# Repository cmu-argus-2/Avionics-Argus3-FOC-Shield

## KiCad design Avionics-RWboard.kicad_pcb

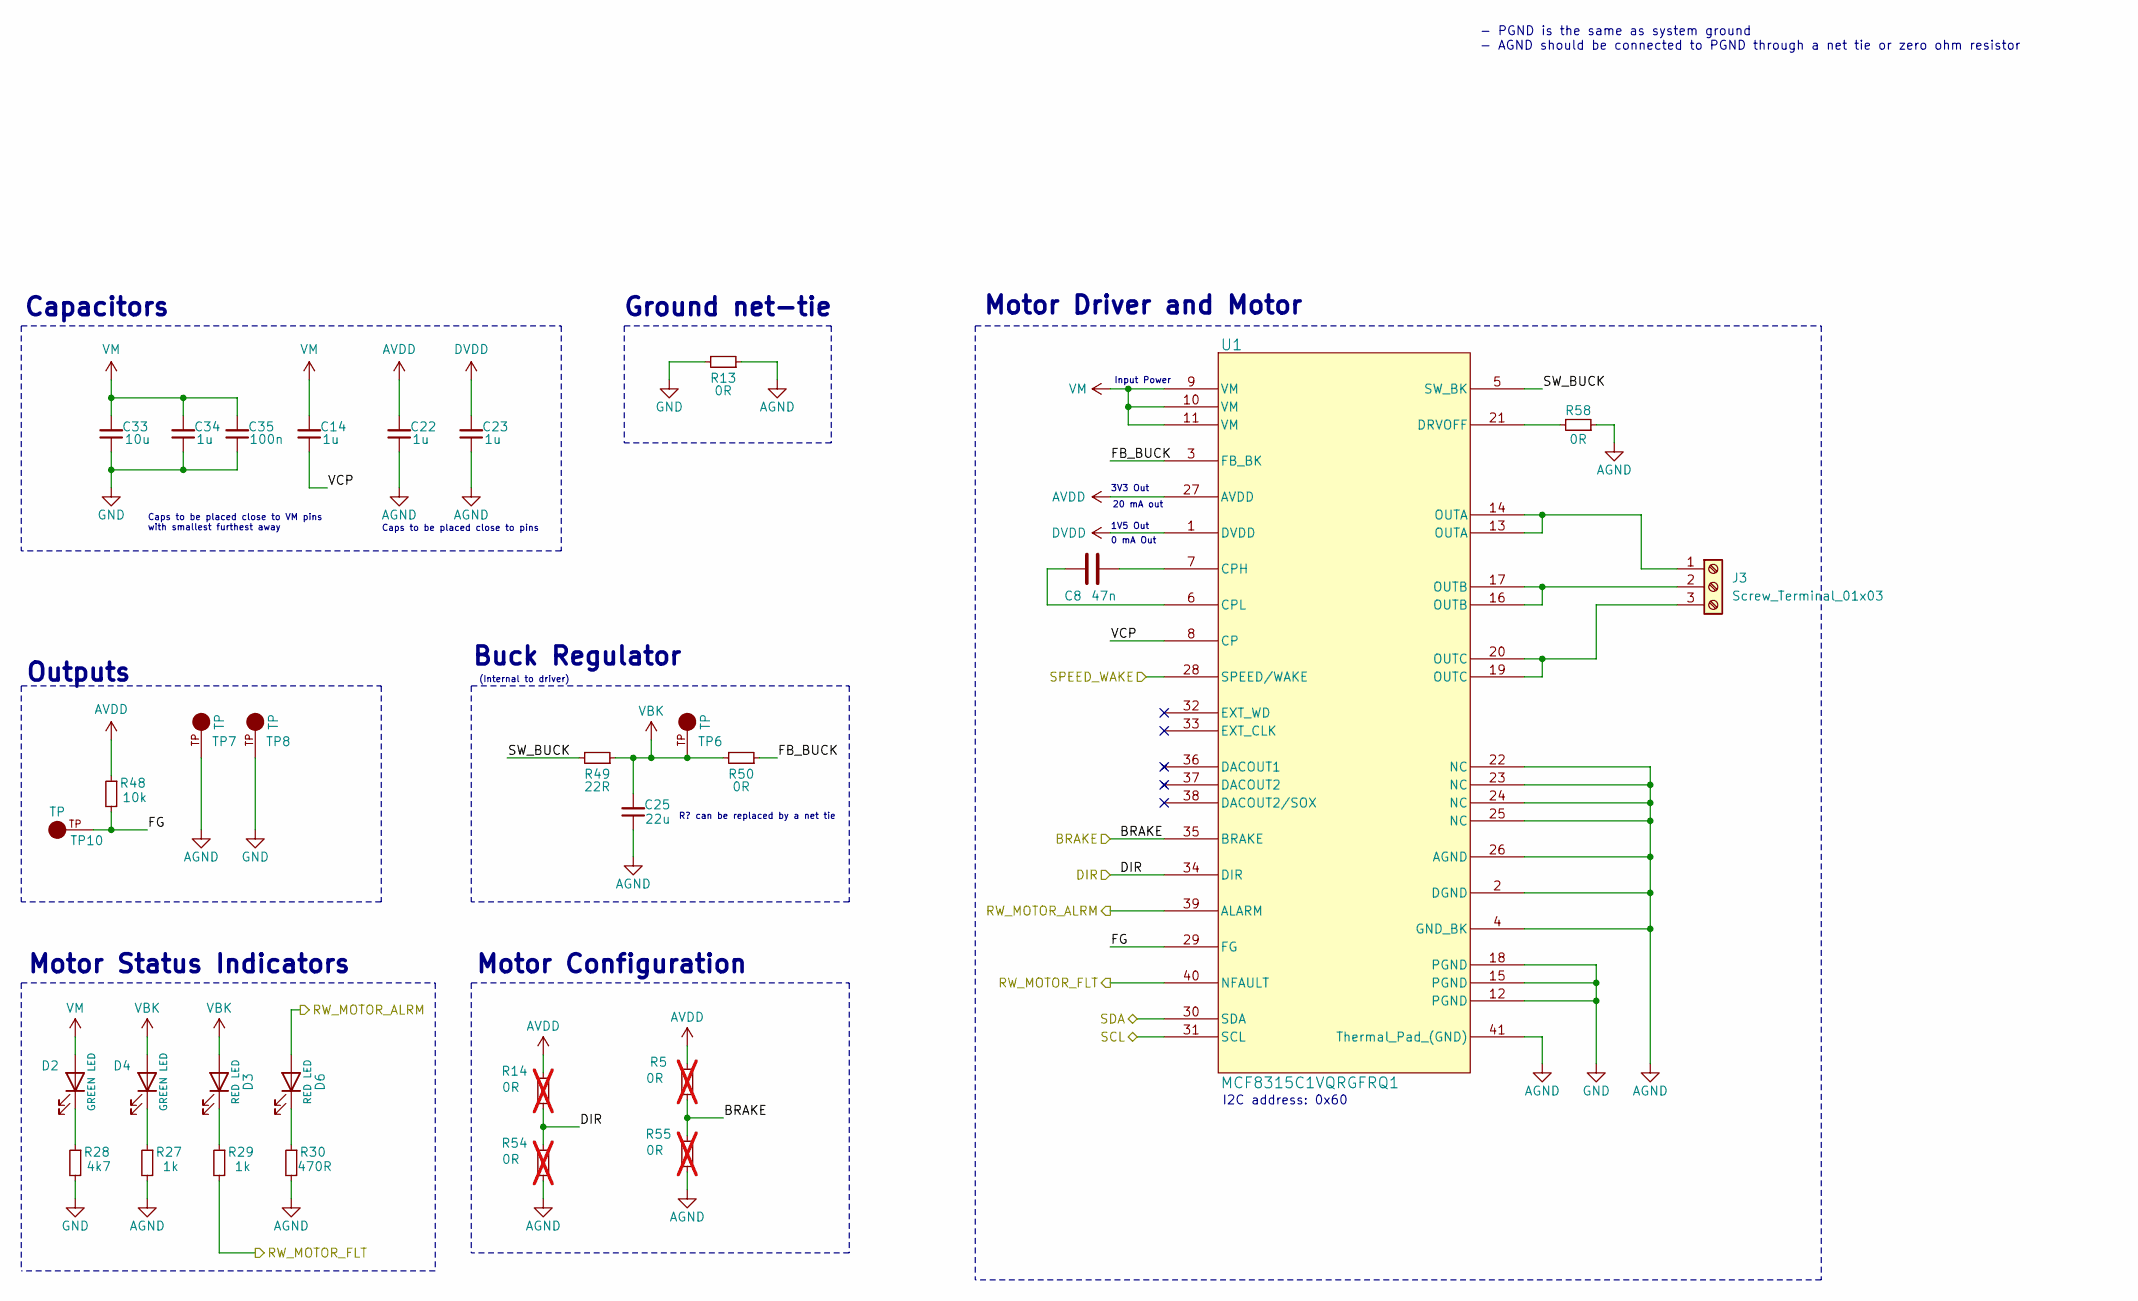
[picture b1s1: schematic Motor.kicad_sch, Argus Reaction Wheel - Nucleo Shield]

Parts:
C8: 47n; C_0603_1608Metric; Part GCM188R71H473KA55D; Digikey PN 490-4934-1-ND
C14, C22, C23, C34: 1u; C_0603_1608Metric; Part CL10B105KA8NNNC; Digikey PN 1276-1184-1-ND
C25: 22u; C_0603_1608Metric; MPN CL10A226MP8NUNE; Digikey PN 1276-1274-1-ND
C33: 10u; C_1206_3216Metric_Pad1.33x1.80mm_HandSolder; Part CL31B106KAHNNNE; Digikey PN 1276-1804-1-ND
C35: 100n; C_0603_1608Metric; Part C0402C103K3RACTU; Digikey PN 399-C0402C103K3RACTUCT-ND
D2, D4: GREEN LED; LED_0603_1608Metric; Manufacturer_Part_Number LTST-C190KGKT; Digikey PN 1830-1064-1-ND
D3, D6: RED LED; LED_0603_1608Metric; Manufacturer_Part_Number LTST-C190KRKT; Digikey PN 1830-1065-1-ND
J3: Screw_Terminal_01x03; TerminalBlock_Phoenix_MKDS-1,5-3_1x03_P5.00mm_Horizontal
R5, R14, R54, R55: 0R; R_0603_1608Metric; MPN RC0402JR-070RL; Digikey PN 311-0.0JRCT-ND; not fitted
R13, R50: 0R; R_0805_2012Metric_Pad1.20x1.40mm_HandSolder; MPN RC0805JR-070RL; Digikey PN 311-0.0ARCT-ND
R27, R29: 1k; R_0603_1608Metric; MPN RC0603FR-071KL; Digikey PN 311-1.00KHRCT-ND
R28: 4k7; R_0603_1608Metric; MPN RC0603FR-074K7L; Digikey PN 311-4.70KHRCT-ND
R30: 470R; R_0603_1608Metric; MPN RC0603FR-13470RL; Digikey PN 13-RC0603FR-13470RLCT-ND
R48: 10k; R_0603_1608Metric; MPN RC0603FR-0710KL; Digikey PN 311-10.0KHRCT-ND
R49: 22R; R_2512_6332Metric_Pad1.40x3.35mm_HandSolder; Part CRCW251222R0FKEGHP; Digikey PN 541-CRCW251222R0FKEGHPCT-ND
R58: 0R; R_0603_1608Metric; MPN RC0402JR-070RL; Digikey PN 311-0.0JRCT-ND
TP6, TP7, TP8, TP10: TP; KEYSTONE_5001; MPN 5001; Digikey PN 36-5001-ND
U1: MCF8315C1VQRGFRQ1; VQFN40_RGF_TEX; MPN MCF8315C1VQRGFRQ1; Digikey PN 296-MCF8315C1VQRGFRQ1CT-ND

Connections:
/Connectors/RW_MOTOR_ALRM: D6.2 (A), U1.39 (ALARM); also elsewhere on the board
/Connectors/RW_MOTOR_FLT: R29.2, U1.40 (NFAULT); also elsewhere on the board
/Connectors/SCL: U1.31 (SCL); also elsewhere on the board
/Connectors/SDA: U1.30 (SDA); also elsewhere on the board
/Connectors/SPEED_WAKE: U1.28 (SPEED/WAKE); also elsewhere on the board
/Motor/BRAKE: R5.1, R55.2, U1.35 (BRAKE); also elsewhere on the board
/Motor/DIR: R14.1, R54.2, U1.34 (DIR); also elsewhere on the board
/Motor/FB_BUCK: R50.1, U1.3 (FB_BK)
/Motor/FG: R48.2, TP10.TP, U1.29 (FG)
/Motor/SW_BUCK: R49.2, U1.5 (SW_BK)
/Motor/VCP: C14.1, U1.8 (CP)
AGND: C22.1, C23.1, C25.1, R13.1, R27.2, R30.2, R54.1, R55.1, R58.1, TP7.TP, U1.2 (DGND), U1.4 (GND_BK), U1.22 (NC), U1.23 (NC), U1.24 (NC), U1.25 (NC), U1.26 (AGND), U1.41 (Thermal_Pad_(GND))
AVDD: C22.2, R5.2, R14.2, R48.1, U1.27 (AVDD)
DVDD: C23.2, U1.1 (DVDD)
GND: C33.1, C34.1, C35.1, R13.2, R28.2, TP8.TP, U1.12 (PGND), U1.15 (PGND), U1.18 (PGND); also elsewhere on the board
unnamed: D2.1 (K), R28.1
unnamed: D3.1 (K), R29.1
unnamed: D4.1 (K), R27.1
unnamed: D6.1 (K), R30.1
unnamed: J3.1, U1.13 (OUTA), U1.14 (OUTA)
unnamed: J3.2, U1.16 (OUTB), U1.17 (OUTB)
unnamed: J3.3, U1.19 (OUTC), U1.20 (OUTC)
unnamed: C8.1, U1.7 (CPH)
unnamed: C8.2, U1.6 (CPL)
unnamed: R58.2, U1.21 (DRVOFF)
VBK: C25.2, D3.2 (A), D4.2 (A), R49.1, R50.2, TP6.TP
VM: C14.2, C33.2, C34.2, C35.2, D2.2 (A), U1.9 (VM), U1.10 (VM), U1.11 (VM); also elsewhere on the board

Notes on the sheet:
20 mA out
3V3 Out
Caps to be placed close to pins
Buck Regulator
0 mA Out
R? can be replaced by a net tie
Input Power
I2C address: 0x60
Motor Driver and Motor
Caps to be placed close to VM pins with smallest furthest away
Ground net-tie
Outputs
1V5 Out
Motor Configuration
- PGND is the same as system ground - AGND should be connected to PGND through a net tie or zero ohm resistor
(Internal to driver)
Motor Status Indicators
Capacitors

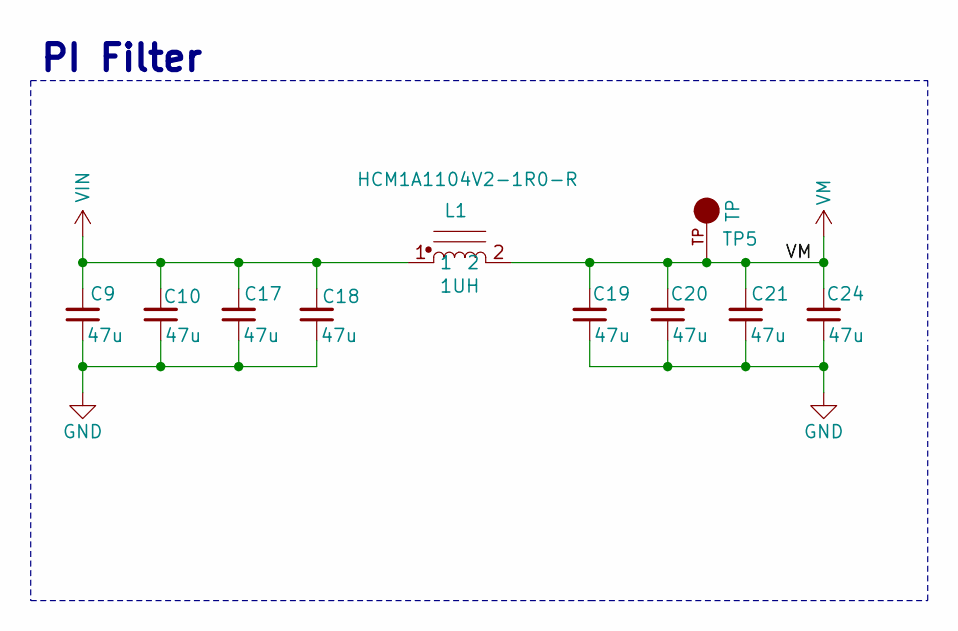
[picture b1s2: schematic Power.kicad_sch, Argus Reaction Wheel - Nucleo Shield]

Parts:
C9, C10, C17, C18, C19, C20, C21, C24: 47u; C_1206_3216Metric_Pad1.33x1.80mm_HandSolder; Part C3216X5R1E476M160AC; Digikey PN 445-8047-1-ND
L1: 1UH; HCM1A1104V2; Part HCM1A1104V2-1R0-R; Digikey PN 283-HCM1A1104V2-1R0-RCT-ND
TP5: TP; KEYSTONE_5001; MPN 5001; Digikey PN 36-5001-ND

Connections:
GND: C9.1, C10.1, C17.1, C18.1, C19.1, C20.1, C21.1, C24.1; also elsewhere on the board
VIN: C9.2, C10.2, C17.2, C18.2, L1.1; also elsewhere on the board
VM: C19.2, C20.2, C21.2, C24.2, L1.2, TP5.TP; also elsewhere on the board

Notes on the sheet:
PI Filter

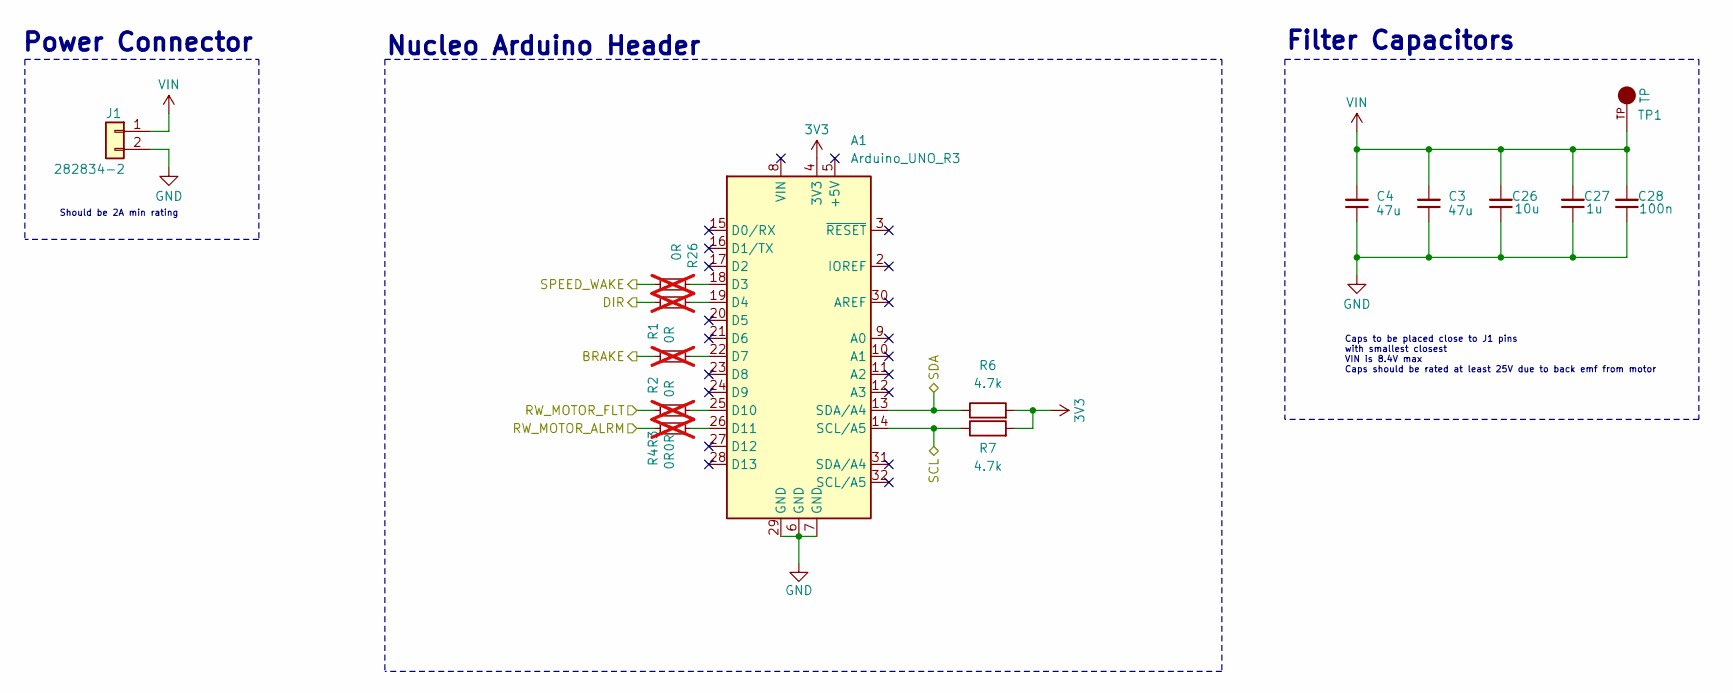
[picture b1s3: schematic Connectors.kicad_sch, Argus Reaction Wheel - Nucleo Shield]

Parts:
A1: Arduino_UNO_R3
C3, C4: 47u; C_1206_3216Metric_Pad1.33x1.80mm_HandSolder; Part C3216X5R1E476M160AC; Digikey PN 445-8047-1-ND
C26: 10u; C_1206_3216Metric_Pad1.33x1.80mm_HandSolder; Part CL31B106KAHNNNE; Digikey PN 1276-1804-1-ND
C27: 1u; C_0603_1608Metric; Part CL10B105KA8NNNC; Digikey PN 1276-1184-1-ND
C28: 100n; C_0603_1608Metric; Part C0402C103K3RACTU; Digikey PN 399-C0402C103K3RACTUCT-ND
J1: 282834-2; TE_282834-2; MPN 282834-2; Digikey PN A98333-ND
R1, R2, R3, R4, R26: 0R; R_0603_1608Metric; MPN RC0402JR-070RL; Digikey PN 311-0.0JRCT-ND; not fitted
R6, R7: 4.7k; R_0603_1608Metric
TP1: TP; KEYSTONE_5001; MPN 5001; Digikey PN 36-5001-ND

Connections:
3V3: A1.4 (3V3), R6.2, R7.2
/Connectors/RW_MOTOR_ALRM: R4.2; also elsewhere on the board
/Connectors/RW_MOTOR_FLT: R3.2; also elsewhere on the board
/Connectors/SCL: A1.14 (SCL/A5), R7.1; also elsewhere on the board
/Connectors/SDA: A1.13 (SDA/A4), R6.1; also elsewhere on the board
/Connectors/SPEED_WAKE: R26.1; also elsewhere on the board
/Motor/BRAKE: R2.2; also elsewhere on the board
/Motor/DIR: R1.2; also elsewhere on the board
GND: A1.6 (GND), A1.7 (GND), A1.29 (GND), C3.1, C4.1, C26.1, C27.1, C28.1, J1.2; also elsewhere on the board
unnamed: A1.18 (D3), R26.2
unnamed: A1.19 (D4), R1.1
unnamed: A1.22 (D7), R2.1
unnamed: A1.25 (D10), R3.1
unnamed: A1.26 (D11), R4.1
VIN: C3.2, C4.2, C26.2, C27.2, C28.2, J1.1, TP1.TP; also elsewhere on the board

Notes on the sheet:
Filter Capacitors
Caps to be placed close to J1 pins with smallest closest VIN is 8.4V max Caps should be rated at least 25V due to back emf from motor
Should be 2A min rating
Power Connector
Nucleo Arduino Header

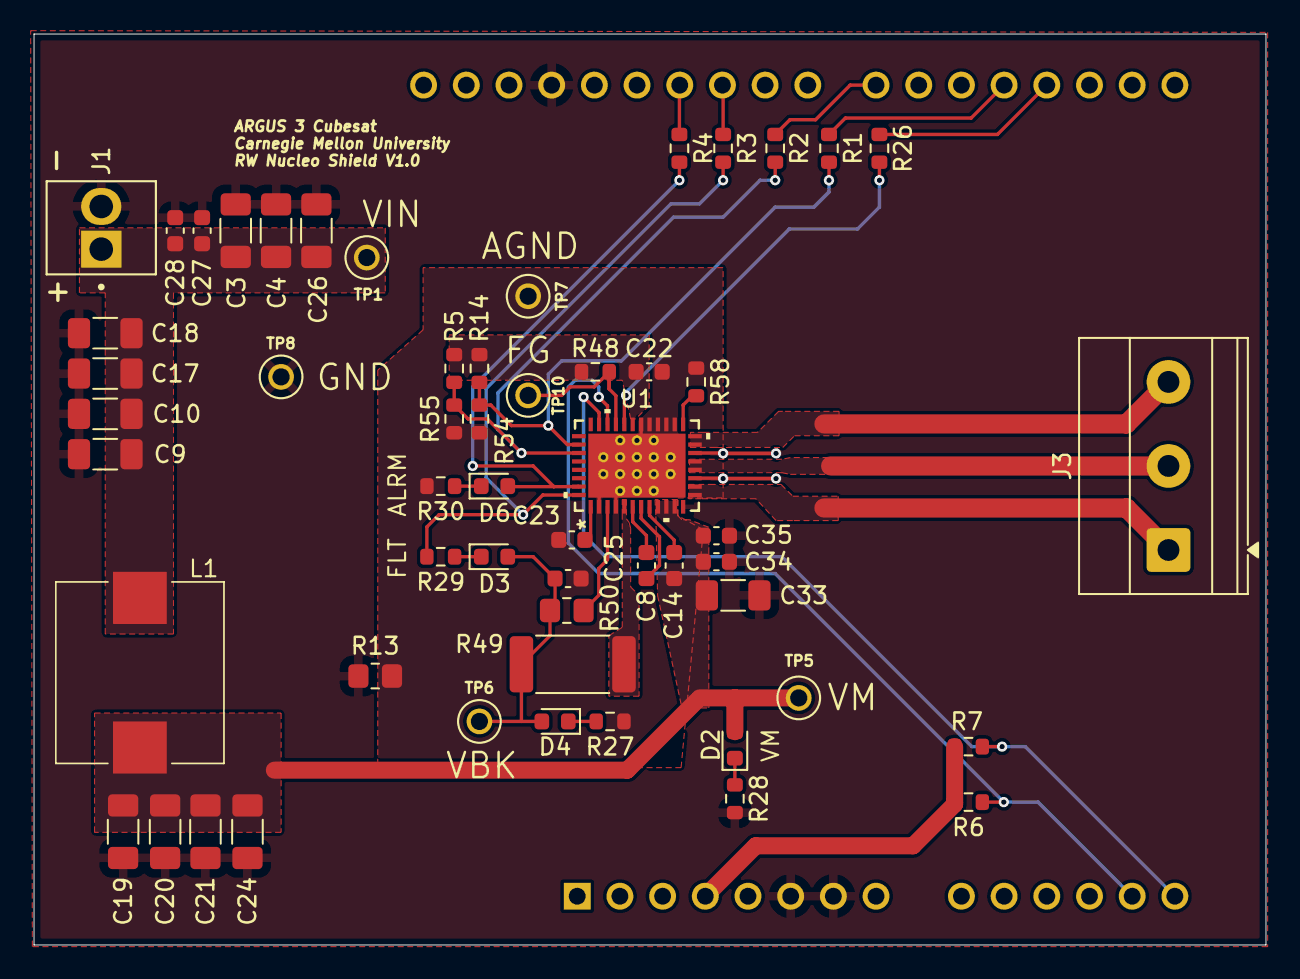
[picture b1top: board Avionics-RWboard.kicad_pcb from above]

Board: 2 copper layers, 73.3 x 54.2 mm, 56 parts (1 on the bottom side), 34 nets.

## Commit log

2026-03-11 fix KiCad-Libraries as submodule
2026-03-17 moved inductor and added leds
2026-03-17 finished board
2026-03-17 added bom
